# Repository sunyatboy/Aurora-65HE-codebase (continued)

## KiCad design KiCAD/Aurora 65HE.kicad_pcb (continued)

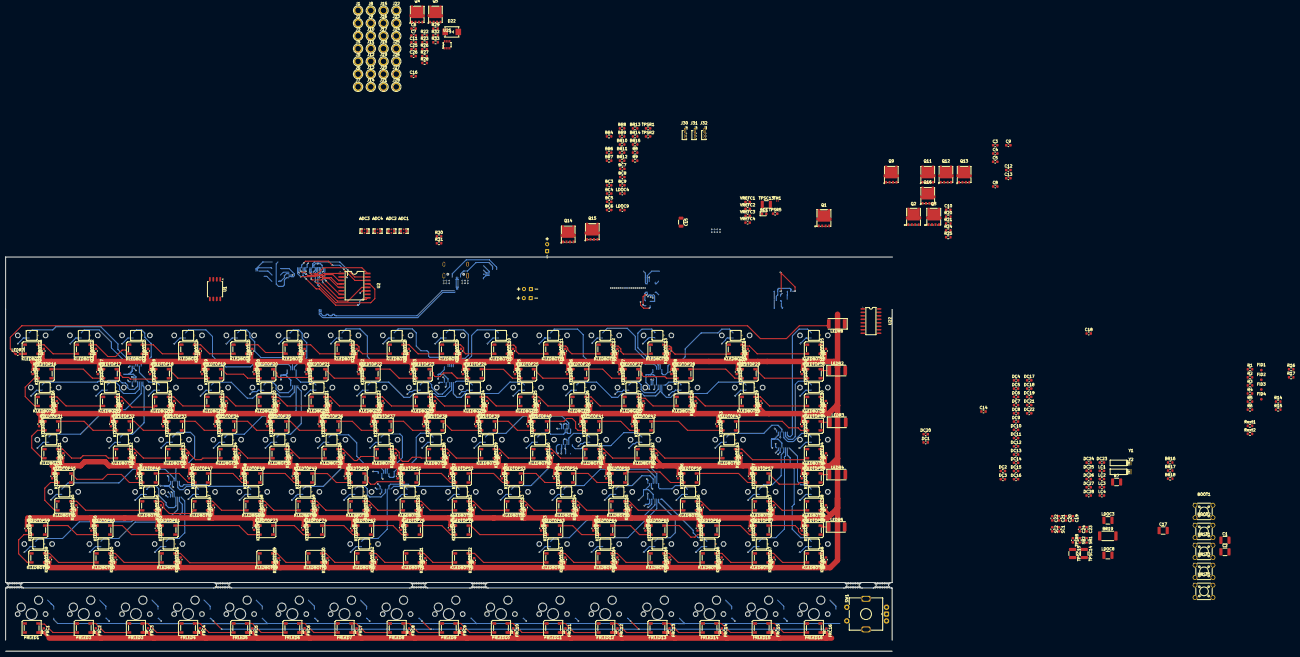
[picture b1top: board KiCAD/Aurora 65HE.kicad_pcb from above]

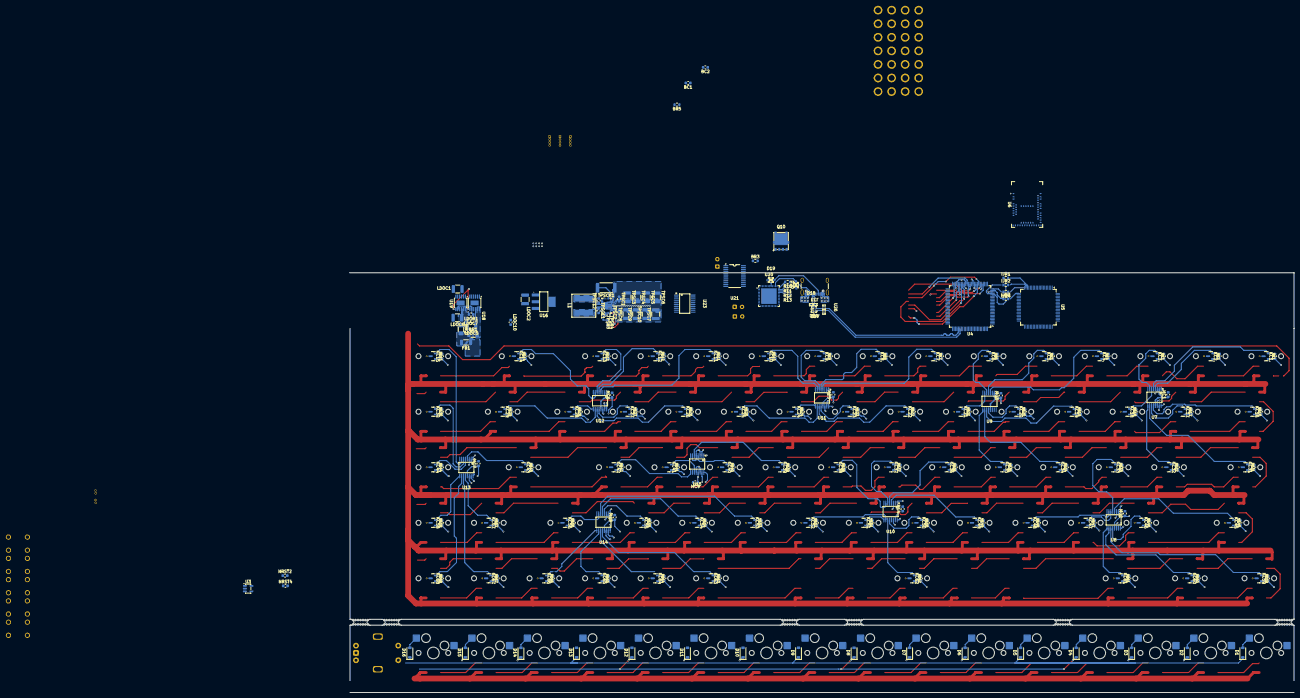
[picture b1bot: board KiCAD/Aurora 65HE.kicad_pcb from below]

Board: 4 copper layers, 324.0 x 144.0 mm, 742 parts (249 on the bottom side), 414 nets.

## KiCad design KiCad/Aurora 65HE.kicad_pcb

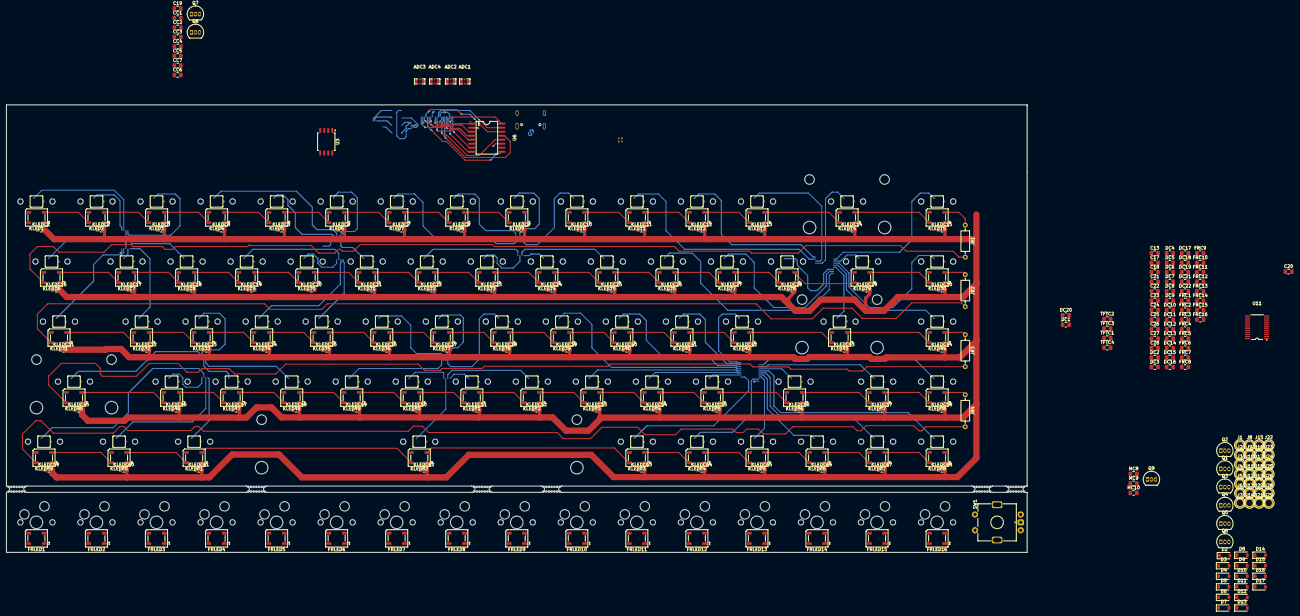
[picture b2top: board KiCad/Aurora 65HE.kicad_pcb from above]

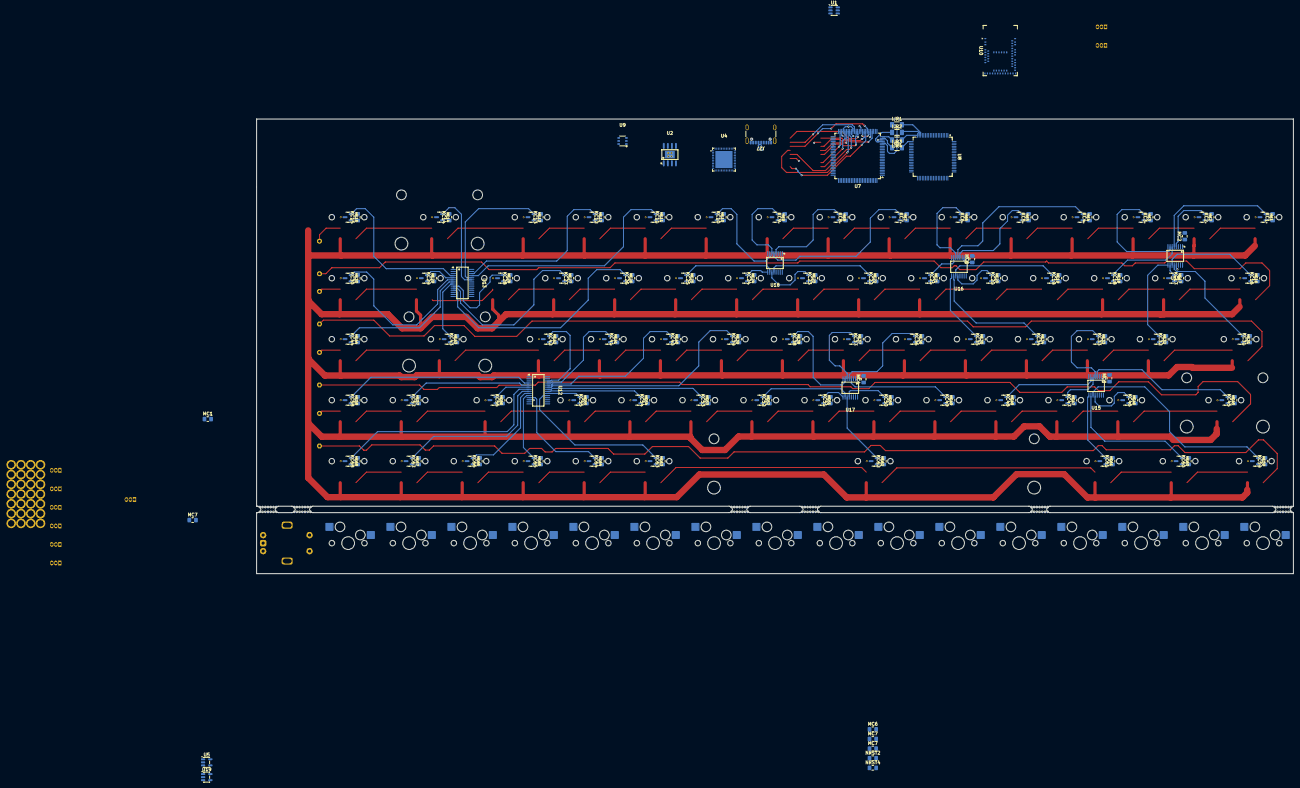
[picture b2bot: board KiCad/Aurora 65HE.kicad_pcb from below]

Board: 4 copper layers, 323.8 x 142.0 mm, 470 parts (184 on the bottom side), 265 nets.

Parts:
ADC1, ADC3: 1uF; FILTER-SMD_4P-L2.0-W1.3_NFM21HC105R1C3D
ADC2, ADC4: 100nF; FILTER-SMD_4P-L2.0-W1.3_NFM21HC105R1C3D
C13, C21, C22, C23, C24, C25, C26, C27, C28: 100nF; C_0805_2012Metric_Pad1.18x1.45mm_HandSolder
C17, C18: 2.2uF; C_0805_2012Metric_Pad1.18x1.45mm_HandSolder
C19, C20: 1uF; C_0805_2012Metric_Pad1.18x1.45mm_HandSolder
CC1, CC2, CC3, CC4, CC5, CC6, CC7: 100nF; C_0805_2012Metric_Pad1.18x1.45mm_HandSolder
D2, D3, D4, D5, D6, D7, D8, D9, D10, D11, D12, D13, D14, D15, D16, D17: D_SOD-123
DC1, DC2, DC3, DC4, DC5, DC6, DC7, DC8, DC9, DC10, DC11, DC12, DC13, DC14, DC15, DC16, DC17, DC18, DC19, DC20, DC21, DC22: 100nF; C_0805_2012Metric_Pad1.18x1.45mm_HandSolder
FRC1, FRC2, FRC3, FRC4, FRC5, FRC6, FRC7, FRC8, FRC9, FRC10, FRC11, FRC12, FRC13, FRC14, FRC15, FRC16: 100nF; C_0805_2012Metric_Pad1.18x1.45mm_HandSolder
FRLED1, FRLED2, FRLED3, FRLED4, FRLED5, FRLED6, FRLED7, FRLED8, FRLED9, FRLED10, FRLED11, FRLED12, FRLED13, FRLED14, FRLED15, FRLED16: WS2812B; LED_WS2812B_PLCC4_5.0x5.0mm_P3.2mm
HE1, HE2, HE3, HE4, HE5, HE6, HE7, HE8, HE9, HE10, HE11, HE12, HE13, HE14, HE15, HE16, HE17, HE18, HE19, HE20, HE21, HE22, HE23, HE24, HE25, HE26, HE27, HE28, HE29, HE30, HE31, HE32, HE33, HE34, HE35, HE36, HE37, HE38, HE39, HE40, HE41, HE42, HE43, HE44, HE45, HE46, HE47, HE48, HE49, HE50, HE51, HE52, HE53, HE54, HE55, HE56, HE57, HE58, HE59, HE60, HE61, HE62, HE63, HE64, HE65, HE66, HE67, HE68: SW_MX_HE; SW_MX_HE_0deg_1u
IJR1, IJR2, IJR3, IJR4: 0; R_1206_3216Metric_Pad1.30x1.75mm_HandSolder
J1, J2: gnd; TestPoint_Plated_Hole_D2.0mm
J3, J4: rotA; TestPoint_Plated_Hole_D2.0mm
J5, J8: rotP; TestPoint_Plated_Hole_D2.0mm
J6, J7: power; TestPoint_Plated_Hole_D2.0mm
J9, J10: rotB; TestPoint_Plated_Hole_D2.0mm
J11, J12: c1; TestPoint_Plated_Hole_D2.0mm
J13, J14: c2; TestPoint_Plated_Hole_D2.0mm
J15, J16: c3; TestPoint_Plated_Hole_D2.0mm
J17, J18: c4; TestPoint_Plated_Hole_D2.0mm
J19, J20: r1; TestPoint_Plated_Hole_D2.0mm
J21, J22: r2; TestPoint_Plated_Hole_D2.0mm
J23, J24: r3; TestPoint_Plated_Hole_D2.0mm
J25, J26: r4; TestPoint_Plated_Hole_D2.0mm
J27: USB_C_Receptacle_USB2.0_16P; USB_C_Receptacle_GCT_USB4105-xx-A_16P_TopMnt_Horizontal
J28, J29: led; TestPoint_Plated_Hole_D2.0mm
JR1, JR2, JR3, JR4: 0; R_Axial_DIN0207_L6.3mm_D2.5mm_P10.16mm_Horizontal
KC1, KC2, KC3, KC4, KC5, KC6, KC7, KC8, KC9, KC10, KC11, KC12, KC13, KC14, KC15, KC16, KC17, KC18, KC19, KC20, KC21, KC22, KC23, KC24, KC25, KC26, KC27, KC28, KC29, KC30, KC31, KC32, KC33, KC34, KC35, KC36, KC37, KC38, KC39, KC40, KC41, KC42, KC43, KC44, KC45, KC46, KC47, KC48, KC49, KC50, KC51, KC52, KC53, KC54, KC55, KC56, KC57, KC58, KC59, KC60, KC61, KC62, KC63, KC64, KC65, KC66, KC67, KC68: 100nF; C_0805_2012Metric_Pad1.18x1.45mm_HandSolder
KLED1, KLED2, KLED3, KLED4, KLED5, KLED6, KLED7, KLED8, KLED9, KLED10, KLED11, KLED12, KLED13, KLED14, KLED15, KLED16, KLED17, KLED18, KLED19, KLED20, KLED21, KLED22, KLED23, KLED24, KLED25, KLED26, KLED27, KLED28, KLED29, KLED30, KLED31, KLED32, KLED33, KLED34, KLED35, KLED36, KLED37, KLED38, KLED39, KLED40, KLED41, KLED42, KLED43, KLED44, KLED45, KLED46, KLED47, KLED48, KLED49, KLED50, KLED51, KLED52, KLED53, KLED54, KLED55, KLED56, KLED57, KLED58, KLED59, KLED60, KLED61, KLED62, KLED63, KLED64, KLED65, KLED66, KLED67, KLED68: WS2812B; LED_WS2812B_PLCC4_5.0x5.0mm_P3.2mm
KLEDC1, KLEDC2, KLEDC3, KLEDC4, KLEDC5, KLEDC6, KLEDC7, KLEDC8, KLEDC9, KLEDC10, KLEDC11, KLEDC12, KLEDC13, KLEDC14, KLEDC15, KLEDC16, KLEDC17, KLEDC18, KLEDC19, KLEDC20, KLEDC21, KLEDC22, KLEDC23, KLEDC24, KLEDC25, KLEDC26, KLEDC27, KLEDC28, KLEDC29, KLEDC30, KLEDC31, KLEDC32, KLEDC33, KLEDC34, KLEDC35, KLEDC36, KLEDC37, KLEDC38, KLEDC39, KLEDC40, KLEDC41, KLEDC42, KLEDC43, KLEDC44, KLEDC45, KLEDC46, KLEDC47, KLEDC48, KLEDC49, KLEDC50, KLEDC51, KLEDC52, KLEDC53, KLEDC54, KLEDC55, KLEDC56, KLEDC57, KLEDC58, KLEDC59, KLEDC60, KLEDC61, KLEDC62, KLEDC63, KLEDC64, KLEDC65, KLEDC66, KLEDC67, KLEDC68: 100nF; C_0805_2012Metric_Pad1.18x1.45mm_HandSolder
MC1, MC2, MC3, MC4, MC5, MC6, MC7, MC7#2, MC7#3, MC8, MC9: 100nF; C_0805_2012Metric_Pad1.18x1.45mm_HandSolder
MC10: 1uF; C_0805_2012Metric_Pad1.18x1.45mm_HandSolder
NRST2, NRST4: 100nF; C_0805_2012Metric_Pad1.18x1.45mm_HandSolder
Q1, Q3, Q4, Q5, Q6, Q7, Q8, Q9: 2N7000; TO-92_Inline
Q2: BS250; TO-92_Inline
S1, S2, S3, S4, S5, S6, S7, S8, S9, S10, S11, S12, S13, S14, S15, S16: MX-Hotswap-1U
S17: MX_stab; STAB_MX_2u
S18, S19: MX_stab; STAB_MX_2.25u
S20: MX_stab; STAB_MX_6.25u
SW1: RotaryEncoder_Switch_MP; ROT_Alps_EC11E-Switch
TFTC1, TFTC4: 10uF; C_0805_2012Metric_Pad1.18x1.45mm_HandSolder
TFTC2, TFTC3: 100nF; C_0805_2012Metric_Pad1.18x1.45mm_HandSolder
U1: USBLC6-2SC6; SOT-23-6
U2: TPS54540DDAR; SOIC-8_L4.9-W3.9-P1.27-LS6.0-BL-EP
U3: W25Q16JVSS; SOIC-8_5.3x5.3mm_P1.27mm
U4: IP2368_I2C_COUT; QFN-48_L7.0-W7.0-P0.50-TL-EP5.4-1
U5, U19: SN74LV1T125DBV; SOT-23-5
U6: MX25LM51245GMI00; SO-16_L10.3-W7.5-P1.27-LS10.3-BL
U7: STM32H7R3V8Tx; LQFP-100_14x14mm_P0.5mm
U8: STM32G474MBTx; LQFP-80_12x12mm_P0.5mm
U9: LTC4412ES6#TRPBF; TSOT-23-6_L2.9-W1.6-P0.95-LS2.8-BR
U10: MDBT50Q-512K; Raytac_MDBT50Q
U11: BQ7791506PW; TSSOP-24_L7.8-W4.4-P0.65-LS6.4-BR
U12, U13: ADG706BRUZ-REEL7; TSSOP-28_L9.7-W4.4-P0.65-LS6.4-BL
U14, U15, U16, U17, U18: ADG708BRUZ_C579091; TSSOP-16_L5.0-W4.4-P0.65-LS6.4-BL

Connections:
+3.3V: DC1.2, DC2.2, DC3.2, DC4.2, DC5.2, DC6.2, DC7.2, DC8.2, DC9.2, DC10.2, DC11.2, DC12.2, DC13.2, DC14.2, DC15.2, DC16.2, DC17.2, DC18.2, DC19.2, DC20.2, DC21.2, DC22.2, MC9.1, MC10.1, TFTC1.1, TFTC2.1, U3.8 (VCC), U6.2 (VCC), U6.11 (VCC), U7.1 (VBAT), U7.9 (VDD), U7.23 (VDD), U7.30 (VDDXSPI1), U7.36 (VDDXSPI1), U7.42 (VDDXSPI1), U7.48 (VDDXSPI1), U7.58 (VDD), U7.69 (VDD), U7.77 (VDD50USB), U7.78 (VDD33USB), U7.85 (VDD), U7.96 (VDD), U8.1 (VBAT), U8.16 (VDD), U8.41 (VDD), U8.51 (VDD), U8.62 (VDD), U8.80 (VDD), U10.28 (VDD), U10.30 (VDDH)
+3.3VA: ADC2.1, ADC3.1, MC1.1, MC2.1, MC3.1, MC4.1, MC5.1, MC6.1, MC7.1, MC7#2.1, MC7#3.1, U12.1 (VDD), U12.18 (EN), U13.1 (VDD), U13.18 (EN), U14.2 (EN), U14.13 (VDD), U15.2 (EN), U15.13 (VDD), U16.2 (EN), U16.13 (VDD), U17.2 (EN), U17.13 (VDD), U18.2 (EN), U18.13 (VDD)
+3.3VADC: ADC1.3, ADC4.3, U7.14 (VREFP), U7.15 (VDDA), U8.28 (VREF+), U8.29 (VDDA)
+5.2VD: FRC1.2, FRC2.2, FRC3.2, FRC4.2, FRC5.2, FRC6.2, FRC7.2, FRC8.2, FRC9.2, FRC10.2, FRC11.2, FRC12.2, FRC13.2, FRC14.2, FRC15.2, FRC16.2, FRLED1.1 (VDD), FRLED2.1 (VDD), FRLED3.1 (VDD), FRLED4.1 (VDD), FRLED5.1 (VDD), FRLED6.1 (VDD), FRLED7.1 (VDD), FRLED8.1 (VDD), FRLED9.1 (VDD), FRLED10.1 (VDD), FRLED11.1 (VDD), FRLED12.1 (VDD), FRLED13.1 (VDD), FRLED14.1 (VDD), FRLED15.1 (VDD), FRLED16.1 (VDD), J6.1 (Pin_1_1), J7.1 (Pin_1_1), KLED1.1 (VDD), KLED2.1 (VDD), KLED3.1 (VDD), KLED4.1 (VDD), KLED5.1 (VDD), KLED6.1 (VDD), KLED7.1 (VDD), KLED8.1 (VDD), KLED9.1 (VDD), KLED10.1 (VDD), KLED11.1 (VDD), KLED12.1 (VDD), KLED13.1 (VDD), KLED14.1 (VDD), KLED15.1 (VDD), KLED16.1 (VDD), KLED17.1 (VDD), KLED18.1 (VDD), KLED19.1 (VDD), KLED20.1 (VDD), KLED21.1 (VDD), KLED22.1 (VDD), KLED23.1 (VDD), KLED24.1 (VDD), KLED25.1 (VDD), KLED26.1 (VDD), KLED27.1 (VDD), KLED28.1 (VDD), KLED29.1 (VDD), KLED30.1 (VDD), KLED31.1 (VDD), KLED32.1 (VDD), KLED33.1 (VDD), KLED34.1 (VDD), KLED35.1 (VDD), KLED36.1 (VDD), KLED37.1 (VDD), KLED38.1 (VDD), KLED39.1 (VDD), KLED40.1 (VDD), KLED41.1 (VDD), KLED42.1 (VDD), KLED43.1 (VDD), KLED44.1 (VDD), KLED45.1 (VDD), KLED46.1 (VDD), KLED47.1 (VDD), KLED48.1 (VDD), KLED49.1 (VDD), KLED50.1 (VDD), KLED51.1 (VDD), KLED52.1 (VDD), KLED53.1 (VDD), KLED54.1 (VDD), KLED55.1 (VDD), KLED56.1 (VDD), KLED57.1 (VDD), KLED58.1 (VDD), KLED59.1 (VDD), KLED60.1 (VDD), KLED61.1 (VDD), KLED62.1 (VDD), KLED63.1 (VDD), KLED64.1 (VDD), KLED65.1 (VDD), KLED66.1 (VDD), KLED67.1 (VDD), KLED68.1 (VDD), KLEDC1.2, KLEDC2.2, KLEDC3.2, KLEDC4.2, KLEDC5.2, KLEDC6.2, KLEDC7.2, KLEDC8.2, KLEDC9.2, KLEDC10.2, KLEDC11.2, KLEDC12.2, KLEDC13.2, KLEDC14.2, KLEDC15.2, KLEDC16.2, KLEDC17.2, KLEDC18.2, KLEDC19.2, KLEDC20.2, KLEDC21.2, KLEDC22.2, KLEDC23.2, KLEDC24.2, KLEDC25.2, KLEDC26.2, KLEDC27.2, KLEDC28.2, KLEDC29.2, KLEDC30.2, KLEDC31.2, KLEDC32.2, KLEDC33.2, KLEDC34.2, KLEDC35.2, KLEDC36.2, KLEDC37.2, KLEDC38.2, KLEDC39.2, KLEDC40.2, KLEDC41.2, KLEDC42.2, KLEDC43.2, KLEDC44.2, KLEDC45.2, KLEDC46.2, KLEDC47.2, KLEDC48.2, KLEDC49.2, KLEDC50.2, KLEDC51.2, KLEDC52.2, KLEDC53.2, KLEDC54.2, KLEDC55.2, KLEDC56.2, KLEDC57.2, KLEDC58.2, KLEDC59.2, KLEDC60.2, KLEDC61.2, KLEDC62.2, KLEDC63.2, KLEDC64.2, KLEDC65.2, KLEDC66.2, KLEDC67.2, KLEDC68.2, U5.5 (VCC), U19.5 (VCC)
+BATT: C22.1, C24.1, Q2.1 (D), U4.26 (CSP2), U4.27 (BAT), U9.1 (VIN)
/1: HE2.2 (VOUT), U14.4 (S1)
/2: HE3.2 (VOUT), U14.7 (S4)
/3: HE4.2 (VOUT), U16.5 (S2)
/4: HE5.2 (VOUT), U16.4 (S1)
/5: HE6.2 (VOUT), U16.6 (S3)
/6: HE7.2 (VOUT), U18.5 (S2)
/7: HE8.2 (VOUT), U18.4 (S1)
/8: HE9.2 (VOUT), U18.6 (S3)
/9: HE10.2 (VOUT), U18.7 (S4)
/10: HE11.2 (VOUT), U13.25 (S7)
/': HE42.2 (VOUT), U12.26 (S8)
/+: HE13.2 (VOUT), U13.24 (S6)
/,: HE53.2 (VOUT), U12.22 (S4)
/-: HE12.2 (VOUT), U13.26 (S8)
/.: HE54.2 (VOUT), U12.21 (S3)
/;: HE41.2 (VOUT), U12.25 (S7)
/[: HE27.2 (VOUT), U13.10 (S10)
/\: HE29.2 (VOUT), U13.5 (S15)
/]: HE28.2 (VOUT), U13.9 (S11)
/`: HE1.2 (VOUT), U14.5 (S2)
/a: HE32.2 (VOUT), U14.9 (S8)
/a0: U14.1 (A0), U15.1 (A0), U16.1 (A0), U17.1 (A0), U18.1 (A0)
/a1: U14.16 (A1), U15.16 (A1), U16.16 (A1), U17.16 (A1), U18.16 (A1)
/a2: U14.15 (A2), U15.15 (A2), U16.15 (A2), U17.15 (A2), U18.15 (A2)
/b: HE50.2 (VOUT), U17.12 (S5)
/backspace: HE14.2 (VOUT), U13.23 (S5)
/bst1: C27.2, U4.17 (BST1)
/bst2: C28.2, U4.22 (BST2)
/c: HE48.2 (VOUT), U15.7 (S4)
/caps: HE31.2 (VOUT), U14.12 (S5)
/cc1: J27.A5 (CC1), U4.41 (CC1)
/cc2: J27.B5 (CC2), U4.38 (CC2)
/csn1: C23.2, U4.14 (CSN1)
/csn2: C24.2, U4.25 (CSN2)
/csp1: C21.1, C23.1, Q1.1 (S), U4.10 (VBUS_I), U4.12 (VIO), U4.13 (CSP1)
/ctrl: HE59.2 (VOUT), U15.11 (S6)
/cts: U7.16 (PA0), U10.20 (P0.04)
/d: HE34.2 (VOUT), U16.10 (S7)
/data+: J27.A6 (D+), J27.B6 (D+), U1.3 (I/O2)
/data-: J27.A7 (D-), J27.B7 (D-), U1.1 (I/O1)
/del: HE30.2 (VOUT), U13.6 (S14)
/downarrow: HE67.2 (VOUT), U12.8 (S12)
/e: HE19.2 (VOUT), U16.11 (S6)
/enter: HE43.2 (VOUT), U13.8 (S12)
/f: HE35.2 (VOUT), U16.9 (S8)
/fn: HE64.2 (VOUT), U12.11 (S9)
/frledin: FRLED1.4 (DIN), U5.4 (Y)
/g: HE36.2 (VOUT), U17.5 (S2)
/gmclk: U3.6 (CLK), U8.17 (PA3)
/h: HE37.2 (VOUT), U17.6 (S3)
/hg1: Q3.2 (G), U4.16 (HG1)
/hg2: Q4.2 (G), U4.23 (HG2)
/i: HE24.2 (VOUT), U18.9 (S8)
/ins: HE15.2 (VOUT), U13.4 (S16)
/interlink NSS: IJR1.2, U8.18 (PA4)
/interlink SCK: IJR2.2, U8.19 (PA5)
/interlink miso: IJR3.2, U8.21 (PA7)
/interlink mosi: IJR4.2, U7.25 (PA7)
/j: HE38.2 (VOUT), U17.7 (S4)
/k: HE39.2 (VOUT), U12.23 (S5)
/l: HE40.2 (VOUT), U12.24 (S6)
/la0: U12.17 (A0), U13.17 (A0)
/la1: U12.16 (A1), U13.16 (A1)
/la2: U12.15 (A2), U13.15 (A2)
/la3: U12.14 (A3), U13.14 (A3)
/lalt: HE61.2 (VOUT), U15.9 (S8)
/leftarrow: HE66.2 (VOUT), U12.9 (S11)
/lg1: Q5.2 (G), U4.19 (LG1)
/lg2: Q6.2 (G), U4.20 (LG2)
/lx1: C27.1, Q3.1 (S), Q5.3 (D), U4.18 (LX1)
/lx2: C28.1, Q4.1 (S), Q6.3 (D), U4.21 (LX2)
/m: HE52.2 (VOUT), U17.10 (S7)
/mclk: U6.16 (SCLK), U7.38 (PO4)
/mcs: U6.7 (~CS), U7.49 (PO0)
/mdqs: U6.13 (DQS), U7.44 (PO2)
/mrst: U6.3 (~RESET), U7.29 (PO1)
/n: HE51.2 (VOUT), U17.9 (S8)
/ntc: C13.1, U4.37 (NTC)
/o: HE25.2 (VOUT), U18.10 (S7)
/p: HE26.2 (VOUT), U13.11 (S9)
/pcin: C25.1, Q3.3 (D), U4.15 (PCIN)
/pcon: C26.1, Q4.3 (D), U4.24 (PCON)
/pgdn: HE58.2 (VOUT), U12.4 (S16)
/pgup: HE44.2 (VOUT), U13.7 (S13)
/q: HE17.2 (VOUT), U14.10 (S7)
/r: HE20.2 (VOUT), U16.12 (S5)
/ralt: HE63.2 (VOUT), U12.19 (S1)
/rctrl: HE65.2 (VOUT), U12.10 (S10)
/rightarrow: HE68.2 (VOUT), U12.7 (S13)
/rshift: HE56.2 (VOUT), U12.6 (S14)
/rst: MC8.1, TFTC3.1
/rts: U7.17 (PA1), U10.21 (P0.05)
/s: HE33.2 (VOUT), U15.5 (S2)
/shift: HE45.2 (VOUT), U15.4 (S1)
/sio0: U6.15 (SI/SIO0), U7.40 (PP0)
/sio1: U6.8 (SO/SIO1), U7.46 (PP1)
/sio2: U6.9 (SIO2), U7.33 (PP2)
/sio3: U6.1 (SIO3), U7.34 (PP3)
/sio4: U6.14 (SIO4), U7.32 (PP4)
/sio5: U6.5 (SIO5), U7.39 (PP5)
/sio6: U6.12 (SIO6), U7.43 (PP6)
/sio7: U6.4 (SIO7), U7.45 (PP7)
/space: HE62.2 (VOUT), U17.11 (S6)
/srn: CC5.1, CC7.2, U11.11 (SRN)
/srp: CC5.2, CC6.2, U11.10 (SRP)
/t: HE21.2 (VOUT), U16.7 (S4)
/tab: HE16.2 (VOUT), U14.11 (S6)
/u: HE23.2 (VOUT), U18.11 (S6)
/uparrow: HE57.2 (VOUT), U12.5 (S15)
/v: HE49.2 (VOUT), U17.4 (S1)
/w: HE18.2 (VOUT), U14.6 (S3)
/wins: HE60.2 (VOUT), U15.10 (S7)
/x: HE47.2 (VOUT), U15.6 (S3)
/y: HE22.2 (VOUT), U18.12 (S5)
/z: HE46.2 (VOUT), U15.12 (S5)
//: HE55.2 (VOUT), U12.20 (S2)
GNDA: ADC1.2, ADC2.2, ADC3.2, ADC4.2, HE1.3 (GND), HE2.3 (GND), HE3.3 (GND), HE4.3 (GND), HE5.3 (GND), HE6.3 (GND), HE7.3 (GND), HE8.3 (GND), HE9.3 (GND), HE10.3 (GND), HE11.3 (GND), HE12.3 (GND), HE13.3 (GND), HE14.3 (GND), HE15.3 (GND), HE16.3 (GND), HE17.3 (GND), HE18.3 (GND), HE19.3 (GND), HE20.3 (GND), HE21.3 (GND), HE22.3 (GND), HE23.3 (GND), HE24.3 (GND), HE25.3 (GND), HE26.3 (GND), HE27.3 (GND), HE28.3 (GND), HE29.3 (GND), HE30.3 (GND), HE31.3 (GND), HE32.3 (GND), HE33.3 (GND), HE34.3 (GND), HE35.3 (GND), HE36.3 (GND), HE37.3 (GND), HE38.3 (GND), HE39.3 (GND), HE40.3 (GND), HE41.3 (GND), HE42.3 (GND), HE43.3 (GND), HE44.3 (GND), HE45.3 (GND), HE46.3 (GND), HE47.3 (GND), HE48.3 (GND), HE49.3 (GND), HE50.3 (GND), HE51.3 (GND), HE52.3 (GND), HE53.3 (GND), HE54.3 (GND), HE55.3 (GND), HE56.3 (GND), HE57.3 (GND), HE58.3 (GND), HE59.3 (GND), HE60.3 (GND), HE61.3 (GND), HE62.3 (GND), HE63.3 (GND), HE64.3 (GND), HE65.3 (GND), HE66.3 (GND), HE67.3 (GND), HE68.3 (GND), KC1.2, KC2.2, KC3.2, KC4.2, KC5.2, KC6.2, KC7.2, KC8.2, KC9.2, KC10.2, KC11.2, KC12.2, KC13.2, KC14.2, KC15.2, KC16.2, KC17.2, KC18.2, KC19.2, KC20.2, KC21.2, KC22.2, KC23.2, KC24.2, KC25.2, KC26.2, KC27.2, KC28.2, KC29.2, KC30.2, KC31.2, KC32.2, KC33.2, KC34.2, KC35.2, KC36.2, KC37.2, KC38.2, KC39.2, KC40.2, KC41.2, KC42.2, KC43.2, KC44.2, KC45.2, KC46.2, KC47.2, KC48.2, KC49.2, KC50.2, KC51.2, KC52.2, KC53.2, KC54.2, KC55.2, KC56.2, KC57.2, KC58.2, KC59.2, KC60.2, KC61.2, KC62.2, KC63.2, KC64.2, KC65.2, KC66.2, KC67.2, KC68.2, MC1.2, MC2.2, MC3.2, MC4.2, MC5.2, MC6.2, MC7.2, MC7#2.2, MC7#3.2, NRST2.1, NRST4.1, U7.12 (VSSA), U8.27 (VSSA), U12.12 (GND), U12.27 (VSS), U13.12 (GND), U13.19 (S1), U13.20 (S2), U13.21 (S3), U13.22 (S4), U13.27 (VSS), U14.3 (VSS), U14.14 (GND), U15.3 (VSS), U15.14 (GND), U16.3 (VSS), U16.14 (GND), U17.3 (VSS), U17.14 (GND), U18.3 (VSS), U18.14 (GND)
GNDD: C13.2, C17.2, C18.2, C19.1, C20.1, C21.2, C22.2, C25.2, C26.2, CC3.1, CC4.1, CC6.1, CC7.1, DC1.1, DC2.1, DC3.1, DC4.1, DC5.1, DC6.1, DC7.1, DC8.1, DC9.1, DC10.1, DC11.1, DC12.1, DC13.1, DC14.1, DC15.1, DC16.1, DC17.1, DC18.1, DC19.1, DC20.1, DC21.1, DC22.1, FRC1.1, FRC2.1, FRC3.1, FRC4.1, FRC5.1, FRC6.1, FRC7.1, FRC8.1, FRC9.1, FRC10.1, FRC11.1, FRC12.1, FRC13.1, FRC14.1, FRC15.1, FRC16.1, FRLED1.3 (VSS), FRLED2.3 (VSS), FRLED3.3 (VSS), FRLED4.3 (VSS), FRLED5.3 (VSS), FRLED6.3 (VSS), FRLED7.3 (VSS), FRLED8.3 (VSS), FRLED9.3 (VSS), FRLED10.3 (VSS), FRLED11.3 (VSS), FRLED12.3 (VSS), FRLED13.3 (VSS), FRLED14.3 (VSS), FRLED15.3 (VSS), FRLED16.3 (VSS), J1.1 (Pin_1_1), J2.1 (Pin_1_1), J27.A1 (GND), J27.A12 (GND), J27.B1 (GND), J27.B12 (GND), J27.SH (SHIELD), KLED1.3 (VSS), KLED2.3 (VSS), KLED3.3 (VSS), KLED4.3 (VSS), KLED5.3 (VSS), KLED6.3 (VSS), KLED7.3 (VSS), KLED8.3 (VSS), KLED9.3 (VSS), KLED10.3 (VSS), KLED11.3 (VSS), KLED12.3 (VSS), KLED13.3 (VSS), KLED14.3 (VSS), KLED15.3 (VSS), KLED16.3 (VSS), KLED17.3 (VSS), KLED18.3 (VSS), KLED19.3 (VSS), KLED20.3 (VSS), KLED21.3 (VSS), KLED22.3 (VSS), KLED23.3 (VSS), KLED24.3 (VSS), KLED25.3 (VSS), KLED26.3 (VSS), KLED27.3 (VSS), KLED28.3 (VSS), KLED29.3 (VSS), KLED30.3 (VSS), KLED31.3 (VSS), KLED32.3 (VSS), KLED33.3 (VSS), KLED34.3 (VSS), KLED35.3 (VSS), KLED36.3 (VSS), KLED37.3 (VSS), KLED38.3 (VSS), KLED39.3 (VSS), KLED40.3 (VSS), KLED41.3 (VSS), KLED42.3 (VSS), KLED43.3 (VSS), KLED44.3 (VSS), KLED45.3 (VSS), KLED46.3 (VSS), KLED47.3 (VSS), KLED48.3 (VSS), KLED49.3 (VSS), KLED50.3 (VSS), KLED51.3 (VSS), KLED52.3 (VSS), KLED53.3 (VSS), KLED54.3 (VSS), KLED55.3 (VSS), KLED56.3 (VSS), KLED57.3 (VSS), KLED58.3 (VSS), KLED59.3 (VSS), KLED60.3 (VSS), KLED61.3 (VSS), KLED62.3 (VSS), KLED63.3 (VSS), KLED64.3 (VSS), KLED65.3 (VSS), KLED66.3 (VSS), KLED67.3 (VSS), KLED68.3 (VSS), KLEDC1.1, KLEDC2.1, KLEDC3.1, KLEDC4.1, KLEDC5.1, KLEDC6.1, KLEDC7.1, KLEDC8.1, KLEDC9.1, KLEDC10.1, KLEDC11.1, KLEDC12.1, KLEDC13.1, KLEDC14.1, KLEDC15.1, KLEDC16.1, KLEDC17.1, KLEDC18.1, KLEDC19.1, KLEDC20.1, KLEDC21.1, KLEDC22.1, KLEDC23.1, KLEDC24.1, KLEDC25.1, KLEDC26.1, KLEDC27.1, KLEDC28.1, KLEDC29.1, KLEDC30.1, KLEDC31.1, KLEDC32.1, KLEDC33.1, KLEDC34.1, KLEDC35.1, KLEDC36.1, KLEDC37.1, KLEDC38.1, KLEDC39.1, KLEDC40.1, KLEDC41.1, KLEDC42.1, KLEDC43.1, KLEDC44.1, KLEDC45.1, KLEDC46.1, KLEDC47.1, KLEDC48.1, KLEDC49.1, KLEDC50.1, KLEDC51.1, KLEDC52.1, KLEDC53.1, KLEDC54.1, KLEDC55.1, KLEDC56.1, KLEDC57.1, KLEDC58.1, KLEDC59.1, KLEDC60.1, KLEDC61.1, KLEDC62.1, KLEDC63.1, KLEDC64.1, KLEDC65.1, KLEDC66.1, KLEDC67.1, KLEDC68.1, MC8.2, MC9.2, MC10.2, Q5.1 (S), Q6.1 (S), Q8.1 (S), Q9.1 (S), SW1.C, SW1.MP, SW1.S2, TFTC1.2, TFTC2.2, TFTC3.2, TFTC4.2, U2.7 (GND), U2.9 (EP), U3.4 (GND), U4.11 (AGND), U4.30 (AGND), U4.47 (ISET_MODE), U4.49 (EP), U5.1 (~OE), U5.3 (GND), U6.6 (GND), U6.10 (GND), U7.8 (VSS), U7.20 (VSS), U7.31 (VSS), U7.35 (VSS), U7.41 (VSS), U7.47 (VSS), U7.57 (VSS), U7.68 (VSS), U7.79 (VSSUSB), U7.95 (VSS), U8.15 (VSS), U8.40 (VSS), U8.50 (VSS), U8.61 (VSS), U8.79 (VSS), U9.2 (GND), U9.3 (CTL), U10.1 (GND), U10.2 (GND), U10.15 (GND), U10.32 (VBUS), U10.33 (GND), U10.55 (GND), U11.9 (VSS), U11.16 (CBI), U11.23 (CTRC), U11.24 (CTRD), U19.1 (~OE), U19.3 (GND)
unnamed: ADC1.1, ADC2.3
unnamed: ADC3.3, ADC4.1
unnamed: D2.2 (A), S1.2
unnamed: D3.2 (A), S2.2
unnamed: D4.2 (A), S3.2
unnamed: D5.2 (A), S4.2
unnamed: D6.2 (A), S5.2
unnamed: D7.2 (A), S6.2
unnamed: D8.2 (A), S7.2
unnamed: D9.2 (A), S8.2
unnamed: D10.2 (A), S9.2
unnamed: D2.1 (K), D6.1 (K), D10.1 (K), D14.1 (K), J19.1 (Pin_1_1)
unnamed: D11.2 (A), S10.2
unnamed: D3.1 (K), D7.1 (K), D11.1 (K), D15.1 (K), J21.1 (Pin_1_1)
unnamed: D12.2 (A), S11.2
unnamed: D4.1 (K), D8.1 (K), D12.1 (K), D16.1 (K), J23.1 (Pin_1_1)
unnamed: D13.2 (A), S12.2
unnamed: D5.1 (K), D9.1 (K), D13.1 (K), D17.1 (K), J25.1 (Pin_1_1)
unnamed: D14.2 (A), S13.2
unnamed: D15.2 (A), S14.2
unnamed: D16.2 (A), S15.2
unnamed: D17.2 (A), S16.2
unnamed: J27.A4 (VBUS), J27.A9 (VBUS), J27.B4 (VBUS), J27.B9 (VBUS)
unnamed: FRLED1.2 (DOUT), FRLED2.4 (DIN)
unnamed: FRLED2.2 (DOUT), FRLED3.4 (DIN)
unnamed: FRLED3.2 (DOUT), FRLED4.4 (DIN)
unnamed: FRLED4.2 (DOUT), FRLED5.4 (DIN)
unnamed: FRLED5.2 (DOUT), FRLED6.4 (DIN)
unnamed: FRLED6.2 (DOUT), FRLED7.4 (DIN)
unnamed: FRLED7.2 (DOUT), FRLED8.4 (DIN)
unnamed: FRLED8.2 (DOUT), FRLED9.4 (DIN)
unnamed: FRLED9.2 (DOUT), FRLED10.4 (DIN)
unnamed: FRLED10.2 (DOUT), FRLED11.4 (DIN)
unnamed: FRLED11.2 (DOUT), FRLED12.4 (DIN)
unnamed: FRLED12.2 (DOUT), FRLED13.4 (DIN)
unnamed: FRLED13.2 (DOUT), FRLED14.4 (DIN)
unnamed: FRLED14.2 (DOUT), FRLED15.4 (DIN)
unnamed: FRLED15.2 (DOUT), FRLED16.4 (DIN)
unnamed: HE1.1 (VCC), HE2.1 (VCC), HE3.1 (VCC), HE4.1 (VCC), HE5.1 (VCC), HE6.1 (VCC), HE7.1 (VCC), HE8.1 (VCC), HE9.1 (VCC), HE10.1 (VCC), HE11.1 (VCC), HE12.1 (VCC), HE13.1 (VCC), HE14.1 (VCC), HE15.1 (VCC), KC1.1, KC2.1, KC3.1, KC4.1, KC5.1, KC6.1, KC7.1, KC8.1, KC9.1, KC10.1, KC11.1, KC12.1, KC13.1, KC14.1, KC15.1
unnamed: HE16.1 (VCC), HE17.1 (VCC), HE18.1 (VCC), HE19.1 (VCC), HE20.1 (VCC), HE21.1 (VCC), HE22.1 (VCC), HE23.1 (VCC), HE24.1 (VCC), HE25.1 (VCC), HE26.1 (VCC), HE27.1 (VCC), HE28.1 (VCC), HE29.1 (VCC), HE30.1 (VCC), KC16.1, KC17.1, KC18.1, KC19.1, KC20.1, KC21.1, KC22.1, KC23.1, KC24.1, KC25.1, KC26.1, KC27.1, KC28.1, KC29.1, KC30.1
unnamed: HE31.1 (VCC), HE32.1 (VCC), HE33.1 (VCC), HE34.1 (VCC), HE35.1 (VCC), HE36.1 (VCC), HE37.1 (VCC), HE38.1 (VCC), HE39.1 (VCC), HE40.1 (VCC), HE41.1 (VCC), HE42.1 (VCC), HE43.1 (VCC), HE44.1 (VCC), KC31.1, KC32.1, KC33.1, KC34.1, KC35.1, KC36.1, KC37.1, KC38.1, KC39.1, KC40.1, KC41.1, KC42.1, KC43.1, KC44.1
unnamed: HE45.1 (VCC), HE46.1 (VCC), HE47.1 (VCC), HE48.1 (VCC), HE49.1 (VCC), HE50.1 (VCC), HE51.1 (VCC), HE52.1 (VCC), HE53.1 (VCC), HE54.1 (VCC), HE55.1 (VCC), HE56.1 (VCC), HE57.1 (VCC), HE58.1 (VCC), KC45.1, KC46.1, KC47.1, KC48.1, KC49.1, KC50.1, KC51.1, KC52.1, KC53.1, KC54.1, KC55.1, KC56.1, KC57.1, KC58.1
unnamed: HE59.1 (VCC), HE60.1 (VCC), HE61.1 (VCC), HE62.1 (VCC), HE63.1 (VCC), HE64.1 (VCC), HE65.1 (VCC), HE66.1 (VCC), HE67.1 (VCC), HE68.1 (VCC), KC59.1, KC60.1, KC61.1, KC62.1, KC63.1, KC64.1, KC65.1, KC66.1, KC67.1, KC68.1
unnamed: J4.1 (Pin_1_1), SW1.A
unnamed: J5.1 (Pin_1_1), SW1.S1
unnamed: J10.1 (Pin_1_1), SW1.B
unnamed: J12.1 (Pin_1_1), S1.1, S2.1, S3.1, S4.1
unnamed: J14.1 (Pin_1_1), S5.1, S6.1, S7.1, S8.1
unnamed: J16.1 (Pin_1_1), S9.1, S10.1, S11.1, S12.1
unnamed: J18.1 (Pin_1_1), S13.1, S14.1, S15.1, S16.1
unnamed: J28.1 (Pin_1_1), U5.2 (A)
unnamed: KLED1.4 (DIN), U19.2 (A)
unnamed: KLED1.2 (DOUT), KLED2.4 (DIN)
unnamed: KLED2.2 (DOUT), KLED3.4 (DIN)
unnamed: KLED3.2 (DOUT), KLED4.4 (DIN)
unnamed: KLED4.2 (DOUT), KLED5.4 (DIN)
unnamed: KLED5.2 (DOUT), KLED6.4 (DIN)
unnamed: KLED6.2 (DOUT), KLED7.4 (DIN)
unnamed: KLED7.2 (DOUT), KLED8.4 (DIN)
unnamed: KLED8.2 (DOUT), KLED9.4 (DIN)
unnamed: KLED9.2 (DOUT), KLED10.4 (DIN)
unnamed: KLED10.2 (DOUT), KLED11.4 (DIN)
unnamed: KLED11.2 (DOUT), KLED12.4 (DIN)
unnamed: KLED12.2 (DOUT), KLED13.4 (DIN)
unnamed: KLED13.2 (DOUT), KLED14.4 (DIN)
unnamed: KLED14.2 (DOUT), KLED15.4 (DIN)
unnamed: JR1.1, KLED15.2 (DOUT)
unnamed: JR1.2, KLED16.4 (DIN)
unnamed: KLED16.2 (DOUT), KLED17.4 (DIN)
unnamed: KLED17.2 (DOUT), KLED18.4 (DIN)
unnamed: KLED18.2 (DOUT), KLED19.4 (DIN)
unnamed: KLED19.2 (DOUT), KLED20.4 (DIN)
unnamed: KLED20.2 (DOUT), KLED21.4 (DIN)
unnamed: KLED21.2 (DOUT), KLED22.4 (DIN)
unnamed: KLED22.2 (DOUT), KLED23.4 (DIN)
unnamed: KLED23.2 (DOUT), KLED24.4 (DIN)
unnamed: KLED24.2 (DOUT), KLED25.4 (DIN)
unnamed: KLED25.2 (DOUT), KLED26.4 (DIN)
unnamed: KLED26.2 (DOUT), KLED27.4 (DIN)
unnamed: KLED27.2 (DOUT), KLED28.4 (DIN)
unnamed: KLED28.2 (DOUT), KLED29.4 (DIN)
unnamed: KLED29.2 (DOUT), KLED30.4 (DIN)
unnamed: JR2.1, KLED30.2 (DOUT)
unnamed: JR2.2, KLED31.4 (DIN)
unnamed: KLED31.2 (DOUT), KLED32.4 (DIN)
unnamed: KLED32.2 (DOUT), KLED33.4 (DIN)
unnamed: KLED33.2 (DOUT), KLED34.4 (DIN)
unnamed: KLED34.2 (DOUT), KLED35.4 (DIN)
unnamed: KLED35.2 (DOUT), KLED36.4 (DIN)
unnamed: KLED36.2 (DOUT), KLED37.4 (DIN)
unnamed: KLED37.2 (DOUT), KLED38.4 (DIN)
unnamed: KLED38.2 (DOUT), KLED39.4 (DIN)
unnamed: KLED39.2 (DOUT), KLED40.4 (DIN)
unnamed: KLED40.2 (DOUT), KLED41.4 (DIN)
unnamed: KLED41.2 (DOUT), KLED42.4 (DIN)
unnamed: KLED42.2 (DOUT), KLED43.4 (DIN)
unnamed: KLED43.2 (DOUT), KLED44.4 (DIN)
unnamed: JR3.1, KLED44.2 (DOUT)
unnamed: JR3.2, KLED45.4 (DIN)
unnamed: KLED45.2 (DOUT), KLED46.4 (DIN)
unnamed: KLED46.2 (DOUT), KLED47.4 (DIN)
unnamed: KLED47.2 (DOUT), KLED48.4 (DIN)
unnamed: KLED48.2 (DOUT), KLED49.4 (DIN)
unnamed: KLED49.2 (DOUT), KLED50.4 (DIN)
unnamed: KLED50.2 (DOUT), KLED51.4 (DIN)
unnamed: KLED51.2 (DOUT), KLED52.4 (DIN)
unnamed: KLED52.2 (DOUT), KLED53.4 (DIN)
unnamed: KLED53.2 (DOUT), KLED54.4 (DIN)
unnamed: KLED54.2 (DOUT), KLED55.4 (DIN)
unnamed: KLED55.2 (DOUT), KLED56.4 (DIN)
unnamed: KLED56.2 (DOUT), KLED57.4 (DIN)
unnamed: KLED57.2 (DOUT), KLED58.4 (DIN)
unnamed: JR4.1, KLED58.2 (DOUT)
unnamed: JR4.2, KLED59.4 (DIN)
unnamed: KLED59.2 (DOUT), KLED60.4 (DIN)
unnamed: KLED60.2 (DOUT), KLED61.4 (DIN)
unnamed: KLED61.2 (DOUT), KLED62.4 (DIN)
unnamed: KLED62.2 (DOUT), KLED63.4 (DIN)
unnamed: KLED63.2 (DOUT), KLED64.4 (DIN)
unnamed: KLED64.2 (DOUT), KLED65.4 (DIN)
unnamed: KLED65.2 (DOUT), KLED66.4 (DIN)
unnamed: KLED66.2 (DOUT), KLED67.4 (DIN)
unnamed: KLED67.2 (DOUT), KLED68.4 (DIN)
unnamed: Q1.2 (G), U4.9 (VBUSG)
unnamed: Q2.2 (G), U9.5 (GATE)
unnamed: Q7.3 (D), Q8.3 (D)
unnamed: C18.1, U4.29 (VCC5V)
unnamed: C17.1, U4.32 (VCCIO)
unnamed: NRST2.2, U7.7 (NRST)
unnamed: IJR1.1, U7.21 (PA4)
unnamed: IJR2.1, U7.22 (PA5)
unnamed: IJR3.1, U7.24 (PA6)
unnamed: IJR4.1, U8.20 (PA6)
unnamed: NRST4.2, U8.7 (PG10)
unnamed: C20.2, U11.2 (AVDD)
unnamed: CC4.2, U11.8 (VC0)
unnamed: CC2.1, CC3.2, U11.7 (VC1)
unnamed: CC1.1, CC2.2, U11.6 (VC2)
unnamed: CC1.2, U11.3 (VC5), U11.4 (VC4), U11.5 (VC3)
unnamed: C19.2, U11.1 (VDD)
VBUS: Q1.3 (D), U4.8 (VBUS)
VCC: Q2.3 (S), U2.2 (VIN), U9.6 (SENSE)
